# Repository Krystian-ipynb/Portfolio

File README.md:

# 📁 Krystian Rozanski | Electrical Engineering Portfolio
### Focus: Power Systems, Electrical Machines, and Grid Infrastructure

Welcome! I am a second-year Electrical Engineering student dedicated to mastering the generation, distribution, and utilization of electrical power. This portfolio documents my technical journey, bridging theoretical electromagnetics with practical system design and simulation.

---

## ⚡ Professional Interests

### 🌐 Grid Infrastructure & Power Systems
Interested in the design and protection of high-voltage transmission and distribution networks. My focus includes substation layouts, protection coordination (relays and sensing), and the integration of renewable energy sources into the existing grid.

### ⚙️ Electrical Machines & Drives
Passionate about the physics and control of rotating machinery. My work includes the study of motor construction, winding configurations, and the numerical modeling of transient characteristics in DC and AC machines.

### 🏢 Building Services & Integrated Systems
Exploring the internal power distribution of commercial and industrial facilities. This includes load calculations, circuit protection, and optimizing electrical systems for efficiency and safety within the built environment.

---

## 📂 Portfolio Organization

* **Engineering Theory:** Analytical work involving vector calculus, electromagnetics, and circuit laws.
* **Modeling & Simulation:** MATLAB and Simulink projects focused on system behavior and performance prediction.
* **Design & Drafting:** Schematic layouts and technical drawings for power distribution and infrastructure.
* **Hands-on Lab Work:** Practical implementation of hardware designs, prototyping, and safety-certified laboratory testing.

---

## 🛠️ Technical Toolkit

* **Analysis:** Power Flow Analysis, Transient Modeling, Protection Schemes.
* **Software:** MATLAB, Simulink, CAD/Drafting software.
* **Safety:** Certified in engineering facility safety and competency protocols.

---

## 📫 Contact & Collaboration

I am always looking to connect with industry professionals, mentors, and fellow engineers.

* **Email:** krystianrozanski@hotmail.com  
* **LinkedIn:** [krystian-rozanski](https://www.linkedin.com/in/krystian-rozanski-643a70262/)

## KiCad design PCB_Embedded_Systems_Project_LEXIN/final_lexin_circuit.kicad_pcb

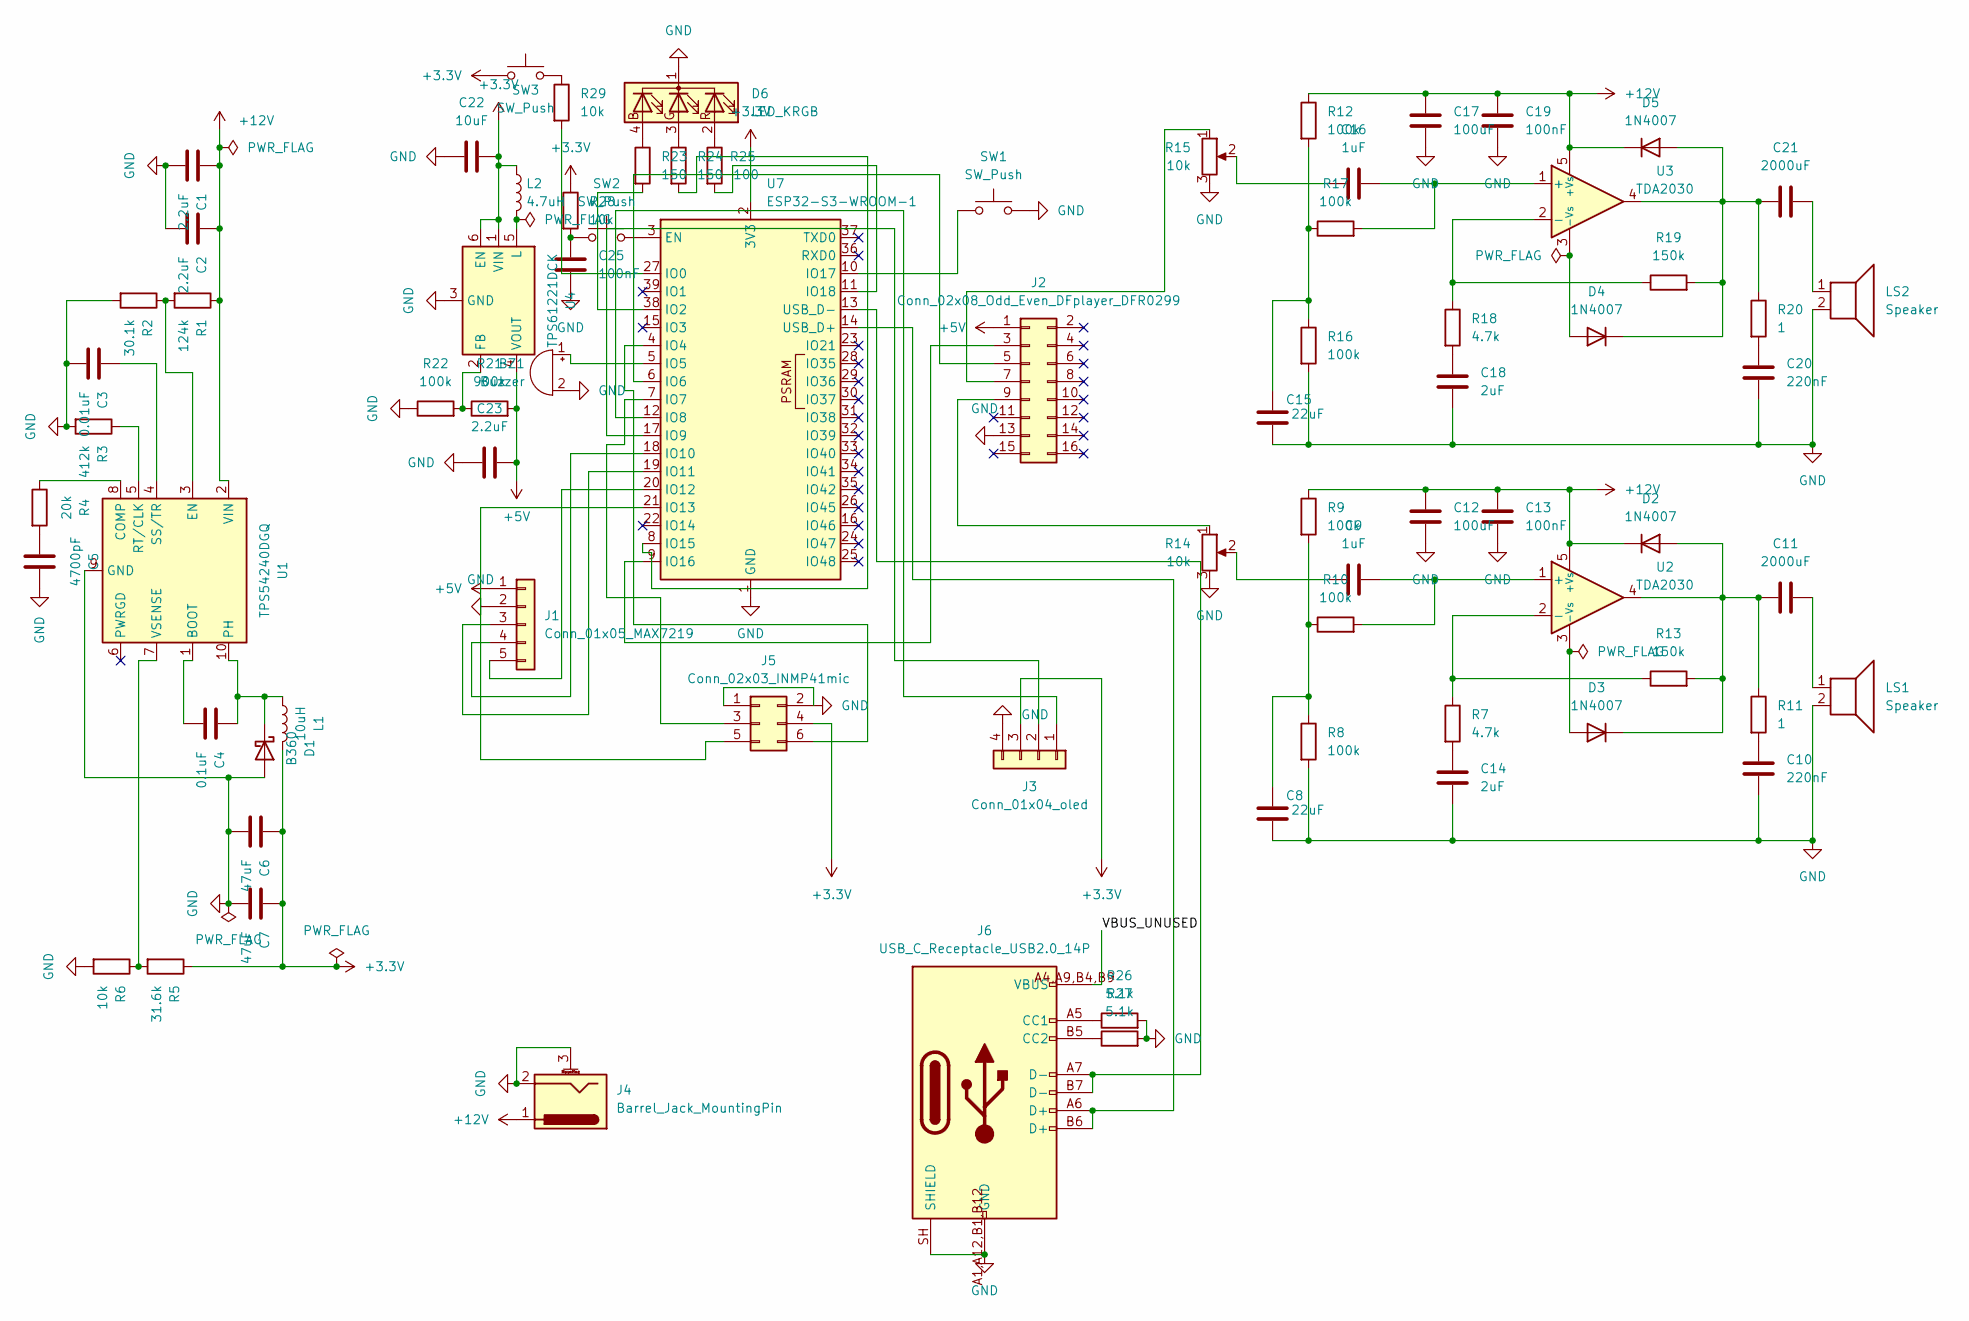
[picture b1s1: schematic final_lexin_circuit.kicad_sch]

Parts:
BZ1: Buzzer; Buzzer_TDK_PS1240P02BT_D12.2mm_H6.5mm; LCSC C76871
C1, C2, C23: 2.2uF; C_0805_2012Metric
C3: 0.01uF; C_0402_1005Metric
C4: 0.1uF; C_0402_1005Metric
C5: 4700pF; C_0402_1005Metric
C6, C7: 47uF; CP_EIA-7343-31_Kemet-D; LCSC C147771
C8, C15: 22uF; C_0805_2012Metric
C9, C16: 1uF; C_0603_1608Metric
C10, C20: 220nF; C_0402_1005Metric
C11, C21: 2000uF; CP_Radial_D10.0mm_P5.00mm; LCSC C400577
C12, C17: 100uF; CP_EIA-7343-31_Kemet-D; LCSC C72478
C13, C19, C25: 100nF; C_0402_1005Metric
C14, C18: 2uF; C_0603_1608Metric
C22: 10uF; C_0805_2012Metric
D1: B360; D_SMC; LCSC C388257
D2, D3, D4, D5: 1N4007; D_SMA; LCSC C232826
D6: LED_KRGB; LED_RGB_1210; LCSC C375571
J1: Conn_01x05_MAX7219; PinSocket_1x05_P2.54mm_Vertical; LCSC C124379
J2: Conn_02x08_Odd_Even_DFplayer_DFR0299; PinSocket_2x08_P2.54mm_Vertical; LCSC C3406
J3: Conn_01x04_oled; PinSocket_1x04_P2.54mm_Vertical; LCSC C124378
J4: Barrel_Jack_MountingPin; BarrelJack_CUI_PJ-102AH_Horizontal; LCSC C3096093
J5: Conn_02x03_INMP41mic; PinSocket_2x03_P2.54mm_Vertical; LCSC C65114
J6: USB_C_Receptacle_USB2.0_14P; USB_C_Receptacle_HCTL_HC-TYPE-C-16P-01A; LCSC C2894897
L1: 10uH; L_Vishay_IFSC-1515AH_4x4x1.8mm; LCSC C844949
L2: 4.7uH; L_Vishay_IFSC-1515AH_4x4x1.8mm; LCSC C844955
LS1, LS2: Speaker; JST_PH_S2B-PH-K_1x02_P2.00mm_Horizontal; LCSC C173752
R1: 124k; R_0402_1005Metric
R2: 30.1k; R_0402_1005Metric
R3: 412k; R_0402_1005Metric
R4: 20k; R_0402_1005Metric
R5: 31.6k; R_0402_1005Metric
R6, R28, R29: 10k; R_0402_1005Metric
R7, R18: 4.7k; R_0402_1005Metric
R8, R9, R10, R12, R16, R17, R22: 100k; R_0402_1005Metric
R11, R20: 1; R_0402_1005Metric
R13, R19: 150k; R_0402_1005Metric
R14, R15: 10k; Potentiometer_Alps_RK09K_Single_Vertical; LCSC C202373
R21: 900k; R_0402_1005Metric
R23, R24: 150; R_0402_1005Metric
R25: 100; R_0402_1005Metric
R26, R27: 5.1k; R_0402_1005Metric
SW1, SW2, SW3: SW_Push; SW_SPST_CK_RS282G05A3; LCSC C221930
U1: TPS54240DGQ; HVSSOP-10-1EP_3x3mm_P0.5mm_EP1.83x1.89mm_ThermalVias; LCSC C53213
U2, U3: TDA2030; TO-220-5_P3.4x3.7mm_StaggerOdd_Lead3.8mm_Vertical; LCSC C2683154
U4: TPS61221DCK; Texas_R-PDSO-G6; LCSC C37055
U7: ESP32-S3-WROOM-1; LCSC C2913202

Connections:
+3.3V: C6.1, C7.1, C22.2, J3.3, J5.4, L1.2, L2.1, R5.1, R28.1, SW3.1, U4.1 (VIN), U4.6 (EN), U7.2 (3V3)
+5V: C23.2, J1.1, J2.1, R21.2, U4.4 (VOUT)
+12V: C1.1, C2.1, C12.1, C13.1, C17.1, C19.1, D2.1 (K), D5.1 (K), J4.1, R1.1, R9.1, R12.1, U1.2 (VIN), U2.5 (+Vs), U3.5 (+Vs)
GND: BZ1.2 (-), C1.2, C2.2, C3.2, C5.2, C6.2, C7.2, C8.2, C10.2, C12.2, C13.2, C14.2, C15.2, C17.2, C18.2, C19.2, C20.2, C22.1, C23.1, C25.1, D1.2 (A), D6.1 (K), J1.2, J2.13, J3.4, J4.2, J4.3 (MountPin_3), J5.1, J5.2, J6.A1 (GND), J6.A1,A12,B1,B12 (GND), J6.A12 (GND), J6.B1 (GND), J6.B12 (GND), J6.SH (SHIELD), LS1.2, LS2.2, R2.2, R3.2, R6.2, R8.2, R14.3, R15.3, R16.2, R22.1, R26.2, R27.2, SW1.2, U1.9 (GND), U1.11 (GND), U4.3 (GND), U7.1 (GND), U7.40 (GND), U7.41 (GND)
unnamed: BZ1.1 (+), U7.5 (IO5)
unnamed: C5.1, R4.2
unnamed: C8.1, R8.1, R9.2, R10.1
unnamed: C9.1, R14.2
unnamed: C10.1, R11.2
unnamed: C11.2, LS1.1
unnamed: C14.1, R7.2
unnamed: C15.1, R12.2, R16.1, R17.1
unnamed: C16.1, R15.2
unnamed: C18.1, R18.2
unnamed: C20.1, R20.2
unnamed: C21.2, LS2.1
unnamed: C25.2, R28.2, SW2.1
unnamed: C4.1, D1.1 (K), L1.1, U1.10 (PH)
unnamed: C11.1, D2.2 (A), D3.1 (K), R11.1, R13.2, U2.4
unnamed: D3.2 (A), U2.3 (-Vs)
unnamed: D4.2 (A), U3.3 (-Vs)
unnamed: C21.1, D4.1 (K), D5.2 (A), R19.2, R20.1, U3.4
unnamed: D6.4 (BA), R23.1
unnamed: D6.3 (GA), R24.1
unnamed: D6.2 (RA), R25.1
unnamed: J1.3, U7.19 (IO11)
unnamed: J1.4, U7.18 (IO10)
unnamed: J1.5, U7.20 (IO12)
unnamed: J2.3, U7.9 (IO16)
unnamed: J2.5, U7.6 (IO6)
unnamed: J2.7, R15.1
unnamed: J2.9, R14.1
unnamed: J3.1, U7.12 (IO8)
unnamed: J3.2, U7.17 (IO9)
unnamed: J5.3, U7.7 (IO7)
unnamed: J5.5, U7.21 (IO13)
unnamed: J5.6, U7.4 (IO4)
unnamed: J6.A5 (CC1), R26.1
unnamed: J6.B5 (CC2), R27.1
unnamed: R29.1, SW3.2
unnamed: C4.2, U1.1 (BOOT)
unnamed: R4.1, U1.8 (COMP)
unnamed: R1.2, R2.1, U1.3 (EN)
unnamed: R3.1, U1.5 (RT/CLK)
unnamed: C3.1, U1.4 (SS/TR)
unnamed: R5.2, R6.1, U1.7 (VSENSE)
unnamed: C9.2, R10.2, U2.1 (+)
unnamed: R7.1, R13.1, U2.2 (-)
unnamed: C16.2, R17.2, U3.1 (+)
unnamed: R18.1, R19.1, U3.2 (-)
unnamed: R21.1, R22.2, U4.2 (FB)
unnamed: L2.2, U4.5 (L)
unnamed: SW2.2, U7.3 (EN)
unnamed: R29.2, U7.27 (IO0)
unnamed: R23.2, U7.38 (IO2)
unnamed: R24.2, U7.8 (IO15)
unnamed: SW1.1, U7.10 (IO17)
unnamed: R25.2, U7.11 (IO18)
unnamed: J6.A6 (D+), J6.B6 (D+), U7.14 (USB_D+)
unnamed: J6.A7 (D-), J6.B7 (D-), U7.13 (USB_D-)

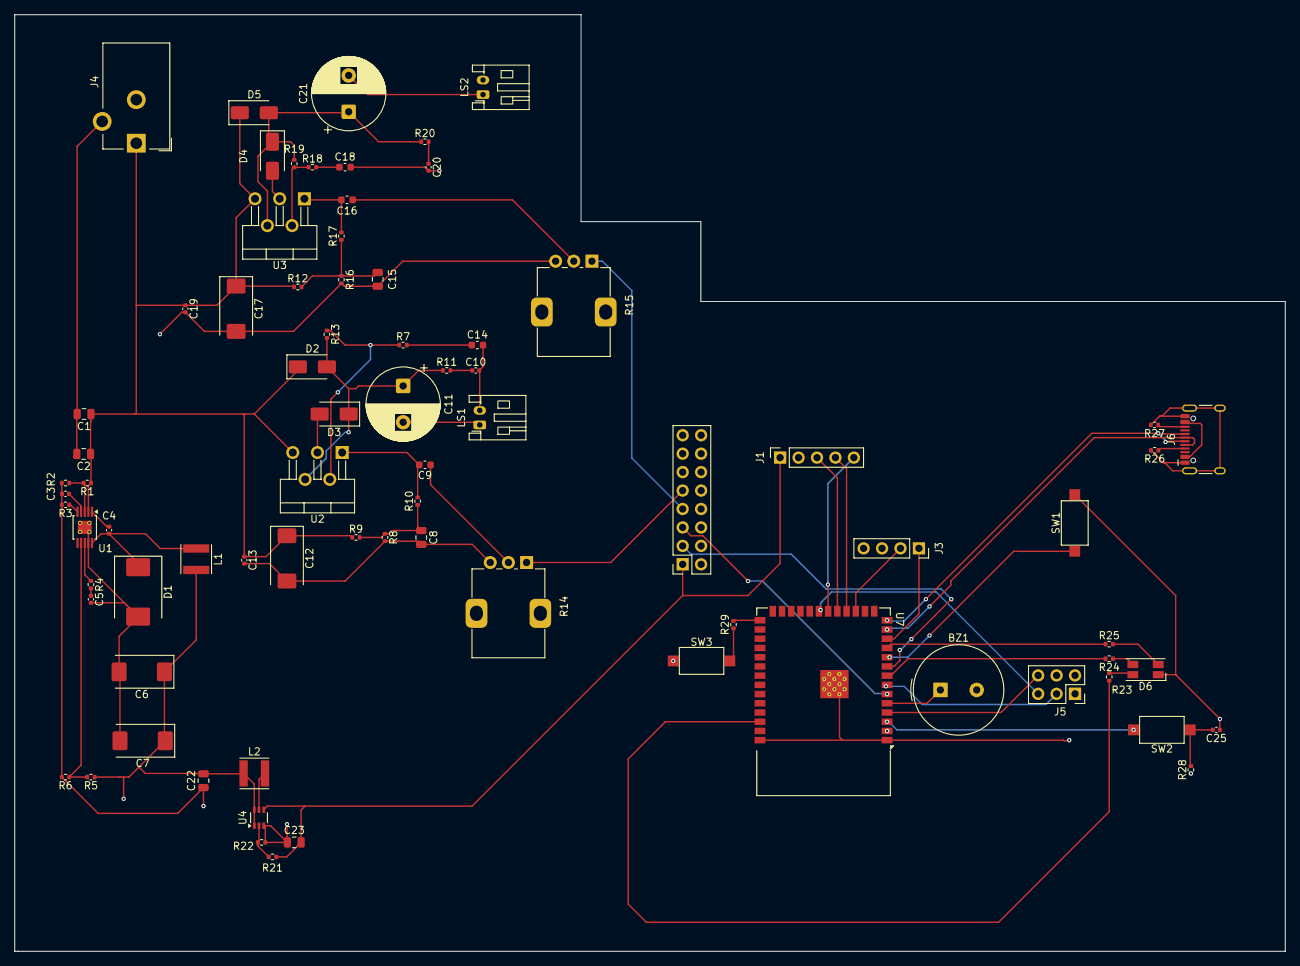
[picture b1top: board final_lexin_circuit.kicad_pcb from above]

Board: 4 copper layers, 175.0 x 129.0 mm, 78 parts (0 on the bottom side), 60 nets.

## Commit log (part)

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2026-04-29 Rename EGB120 Assignment - Circuit Analysis Final.pdf to Year-1-Projects/EGB120 Assignment - Circuit Analysis Final.pdf
2026-04-29 Rename computational_algorithms.ipynb to Year-1-Projects/computational_algorithms.ipynb
2026-04-29 Rename flight_simulator.ipynb to Year-1-Projects/flight_simulator.ipynb
2026-04-29 Rename pandas_data_analysis.ipynb to Year-1-Projects/pandas_data_analysis.ipynb
2026-04-29 Rename research_stochastic_gradient_ML_smart_grids.pdf to Year-1-Projects/research_stochastic_gradient_ML_smart_grids.pdf
2026-04-29 Rename wali_presentation_script.pdf to Year-1-Projects/wali_presentation_script.pdf
2026-04-29 Rename wali_presentation_slides.pdf to Year-1-Projects/wali_presentation_slides.pdf
2026-04-29 Rename wali_project_final_report.pdf to Year-1-Projects/wali_project_final_report.pdf
2026-04-29 Create f
2026-06-12 Rename Year-2-Projects/f to Year-2-Projects/Microcontroller Assignment/src
2026-06-12 Create include
2026-06-12 Rename Year-2-Projects/EGB241 Assignment Documentation.docx to Year-2-Projects/Motor Project/EGB241 Assignment Documentation.docx
2026-06-12 Rename Year-2-Projects/EGB241 Krystian Rozanski Motor Reflection.docx to Year-2-Projects/Motor Project/EGB241 Krystian Rozanski Motor Reflection.docx
2026-06-12 Rename Year-2-Projects/EGB241_EXCEL_ASSIGNMENT_INTERFACE(1).xlsx to Year-2-Projects/Motor Project/EGB241_EXCEL_ASSIGNMENT_INTERFACE(1).xlsx
